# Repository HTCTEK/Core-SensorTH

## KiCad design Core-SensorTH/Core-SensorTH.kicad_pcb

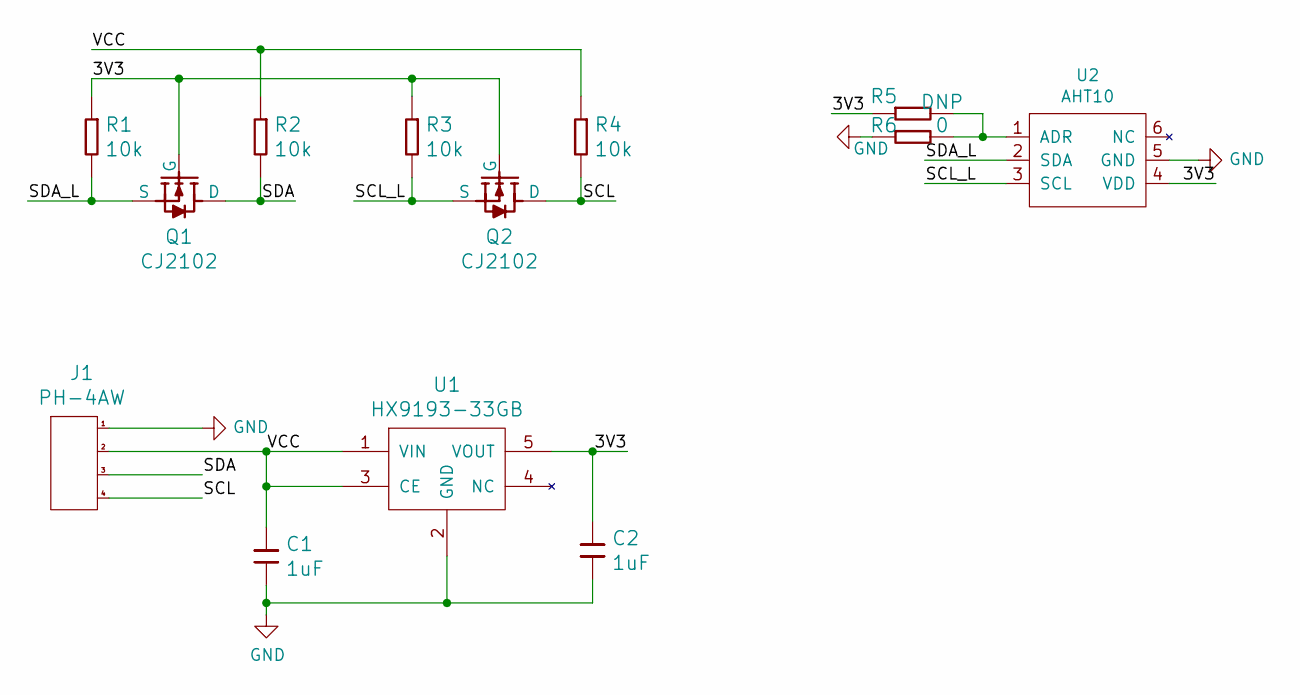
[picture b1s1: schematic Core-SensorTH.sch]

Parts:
C1, C2: 1uF; C_0402_1005Metric; PartNumber GRM155R61A105KE01D
J1: PH-4AW; JST_PH_S4B-PH-K_1x04_P2.00mm_Horizontal; PartNumber PH-4AW
Q1, Q2: CJ2102; SOT-323_SC-70; PartNumber CJ2102
R1, R2, R3, R4: 10k; R_0402_1005Metric; PartNumber 0402WGF1002TCE
R5: DNP; R_0402_1005Metric; PartNumber 0402WGJ0000TCE
R6: 0; R_0402_1005Metric; PartNumber 0402WGJ0000TCE
U1: HX9193-33GB; SOT-23-5; PartNumber HX9193-33GB
U2: AHT10; Temperature_Humidity_Sensor_ASAIR_AHT10_4x5x1.6mm; PartNumber AHT10

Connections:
/3V3: C2.1, Q1.1 (G), Q2.1 (G), R1.1, R3.1, R5.1, U1.5 (VOUT), U2.4 (VDD)
/SCL: J1.4, Q2.3 (D), R4.2
/SCL_L: Q2.2 (S), R3.2, U2.3 (SCL)
/SDA: J1.3, Q1.3 (D), R2.2
/SDA_L: Q1.2 (S), R1.2, U2.2 (SDA)
/VCC: C1.1, J1.2, R2.1, R4.1, U1.1 (VIN), U1.3 (CE)
GND: C1.2, C2.2, J1.1, R6.1, U1.2 (GND), U2.5 (GND)
unnamed: R5.2, R6.2, U2.1 (ADR)

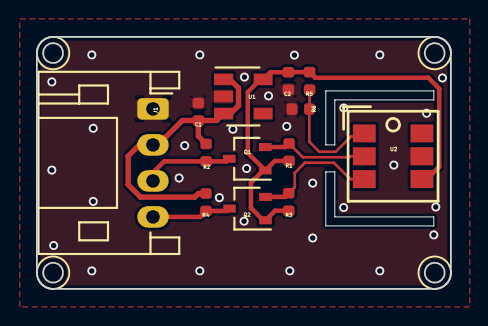
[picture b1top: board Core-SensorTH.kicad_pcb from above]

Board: 2 copper layers, 23.0 x 14.0 mm, 13 parts (0 on the bottom side), 8 nets.

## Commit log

2020-02-29 v0.1 打样
2020-02-29 增加readme
2020-02-29 修改readme
2020-02-29 增加接口丝印标识
